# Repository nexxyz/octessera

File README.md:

# Octessera

Octessera turns cellular automata into music you can play.

It is a collection of small algorithmic musical world-bubbles. Set up a few
systems, combine them, nudge them, anchor them with a little sequencing, and
perform with the result in real time. The little rule-based worlds surprise
you, and you decide which surprises to keep.

## Start here

- [Try the simulator](userdocs/desktop-simulator.md): make a sound without
  building any hardware.
- [Build the instrument](userdocs/hardware/assembly-manual.md): assemble a
  standalone Octessera around a Raspberry Pi Zero 2 W or an Orange Pi Zero 2W.

The standalone instrument is built on exactly one of those two boards, with an
8x8 light-up grid, four keys, encoders, an OLED, and a DAC. The desktop
simulator mirrors the same instrument, so you can explore it on a computer
before you warm up the soldering iron.

## What you can make

- Grow generative synth patterns from Life, Brain, Ant, Bounce, Raindrops, and
  other cellular-automata behaviors.
- Make hands-on drum sequences, load samples, and send parts to external MIDI
  gear.
- Layer up to eight instruments and let grid motion reshape another layer's
  pitch, filter, velocity, or probability through modulation.
- Route instruments directly or through FX buses, then shape the shared mix with
  bus and global effects.
- Use **Keys** to play a line live, and use **Play** pages to mix, pan, change
  trigger probability, move XY controls, and punch in momentary effects.

A first session might be a drifting `life` pattern under a hand-built drum
sequence, with a sampler providing the hits, a bus effect making room for the
synth, and a live Keys layer nudging the whole thing somewhere new.

## Two reading guides

- [User guide](userdocs/README.md): the simulator, building and setting up the
  hardware, making music, controls, and reference pages. Start here if you want
  to play or build one.
- [Technical guide](docs/README.md): architecture, contracts, the two fixed
  board paths, build and deployment tools, and provenance. Start here if you
  want to change the code.

## Notes

[License](LICENSE) · [Sample pack](https://github.com/stargatedaw/stargate-sample-pack) ·
[Hardware attributions](hardware/ATTRIBUTIONS.md) ·
[Third-party notices](THIRD_PARTY_NOTICES.md)

This project was created with AI assistance. Octessera itself, however, does not contain any AI.

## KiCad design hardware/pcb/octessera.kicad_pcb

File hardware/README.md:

# Hardware

This is the home for Octessera's canonical hardware sources and committed
fabrication outputs. Building one? Start with the [assembly
manual](../userdocs/hardware/assembly-manual.md) instead; this tree is the
workshop behind it.

## What's in here

- [`hardware/pcb/`](pcb/) is the canonical KiCad source and library tree.
- [`hardware/enclosure/`](enclosure/) is the canonical CadQuery, generator, test, wrapper,
  and workflow source tree.
- [`hardware/docs/`](docs/) holds the technical references:
  - [Pinout and connections](docs/pinout-and-connections.md): PCB nets, buses,
    addresses and the `J1` cable.
  - [Manual hardware test suite](docs/manual-hardware-test-suite.md):
    Raspberry bench bring-up without the OLED.
  - [Orange Pi Armbian bring-up](docs/orange-pi-armbian-bringup.md), the
    [Orange production reference](docs/orange-pi-production-reference.md) and
    [Orange UART0 input routing](docs/orange-pi-input-routing.md).
  - [Branding assets](docs/branding-assets.md): logo sources and where they end
    up.

## PCB outputs

[`hardware/pcb/gerber/`](pcb/gerber/) contains the committed fabrication output: Gerbers,
drill files, the KiCad job file, and [`gerber.zip`](pcb/gerber/gerber.zip).

## Enclosure outputs

The enclosure source tree includes
[`CAD_WORKFLOW.md`](enclosure/CAD_WORKFLOW.md) and the CadQuery generators,
tests, and wrappers. It commits four generated output sets of 18 files each:

- [`hardware/enclosure/step/`](enclosure/step/): STEP files;
- [`hardware/enclosure/stl/`](enclosure/stl/): printable STL files;
- [`hardware/enclosure/3mf-single-material/`](enclosure/3mf-single-material/): single-material 3MF files;
- [`hardware/enclosure/3mf-multicolor/`](enclosure/3mf-multicolor/): multicolor 3MF files.

The multicolor set is a complete print set: 12 authored two-material designs
plus six one-material support pieces.

Protective-case filenames are canonical and statusless (`protective_case_*`).
The design remains an unqualified check-fit prototype, not a drop-rated,
waterproof, or transport-qualified product.

## Attribution and notices

See also:

- [`hardware/ATTRIBUTIONS.md`](ATTRIBUTIONS.md)
- [`NOTICE`](../NOTICE)
- [`THIRD_PARTY_NOTICES.md`](../THIRD_PARTY_NOTICES.md)
- [`samples/upstream/LICENSE`](../samples/upstream/LICENSE)

## Release assets

GitHub Desktop and Pi release assets are built by the release workflows and are
not stored here. This tree contains the canonical hardware sources and
committed fabrication outputs only.

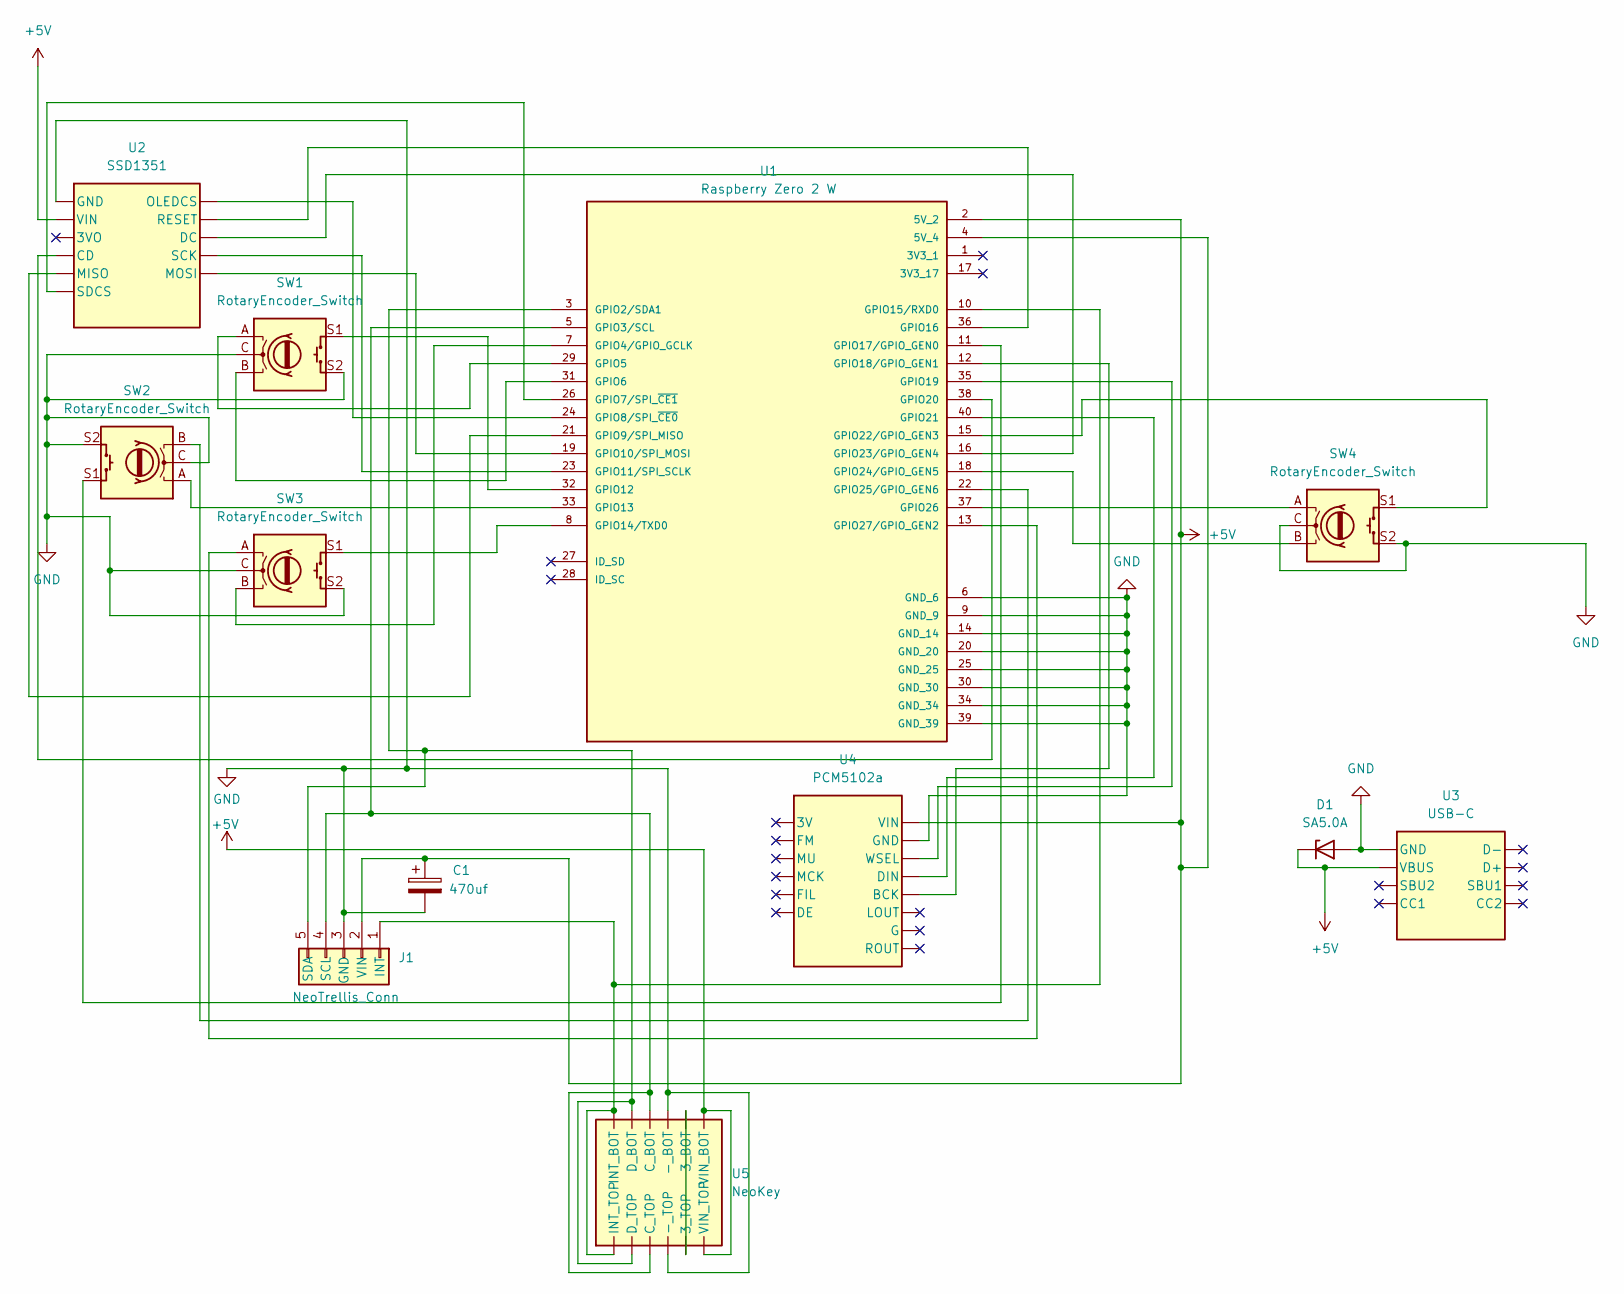
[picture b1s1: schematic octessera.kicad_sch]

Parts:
C1: 470uf; CP_Radial_D8.0mm_P3.50mm
D1: SA5.0A; D_DO-15_P10.16mm_Horizontal
J1: NeoTrellis_Conn; Adafruit_NeoTrellis_Connector_1x5
SW1, SW2, SW3, SW4: RotaryEncoder_Switch; RotaryEncoder_Alps_EC11E-Switch_Vertical_H20mm
U1: Raspberry Zero 2 W; MODULE_RASPBERRY_PI_ZERO_2_W; PARTREV April 2024
U2: SSD1351; Adafruit_SSD1351_OLED
U3: USB-C; Adafruit_USB_C_Breakout
U4: PCM5102a; Adafruit_PCM510x_I2S_DAC_6250
U5: NeoKey; Adafruit_NeoKey_1x4_QT

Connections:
+5V: C1.1, D1.1 (K), J1.2 (VIN), U1.2 (5V_2), U1.4 (5V_4), U2.+ (VIN), U3.VBUS, U4.VIN, U5.VIN (VIN_TOP)
GND: C1.2, D1.2 (A), J1.3 (GND), SW1.C, SW1.S2, SW2.C, SW2.S2, SW3.C, SW3.S2, SW4.C, SW4.S2, U1.6 (GND_6), U1.9 (GND_9), U1.14 (GND_14), U1.20 (GND_20), U1.25 (GND_25), U1.30 (GND_30), U1.34 (GND_34), U1.39 (GND_39), U2.G (GND), U3.GND, U4.GND, U5.- (-_TOP)
unnamed: J1.1 (INT), U1.10 (GPIO15/RXD0), U5.INT (INT_TOP)
unnamed: J1.4 (SCL), U1.5 (GPIO3/SCL), U5.C (C_TOP)
unnamed: J1.5 (SDA), U1.3 (GPIO2/SDA1), U5.D (D_TOP)
unnamed: SW3.B, U1.7 (GPIO4/GPIO_GCLK)
unnamed: SW1.A, U1.29 (GPIO5)
unnamed: SW1.B, U1.31 (GPIO6)
unnamed: U1.26 (GPIO7/SPI_~CE1), U2.SC (SDCS)
unnamed: U1.24 (GPIO8/SPI_~CE0), U2.OC (OLEDCS)
unnamed: U1.21 (GPIO9/SPI_MISO), U2.SO (MISO)
unnamed: U1.19 (GPIO10/SPI_MOSI), U2.SI (MOSI)
unnamed: U1.23 (GPIO11/SPI_SCLK), U2.CL (SCK)
unnamed: SW1.S1, U1.32 (GPIO12)
unnamed: SW2.A, U1.33 (GPIO13)
unnamed: SW3.S1, U1.8 (GPIO14/TXD0)
unnamed: U1.36 (GPIO16), U2.R (RESET)
unnamed: SW2.S1, U1.11 (GPIO17/GPIO_GEN0)
unnamed: U1.12 (GPIO18/GPIO_GEN1), U4.BCK
unnamed: U1.35 (GPIO19), U4.WSEL
unnamed: U1.38 (GPIO20), U2.CD
unnamed: U1.40 (GPIO21), U4.DIN
unnamed: SW4.S1, U1.15 (GPIO22/GPIO_GEN3)
unnamed: U1.16 (GPIO23/GPIO_GEN4), U2.DC
unnamed: SW4.B, U1.18 (GPIO24/GPIO_GEN5)
unnamed: SW2.B, U1.22 (GPIO25/GPIO_GEN6)
unnamed: SW4.A, U1.37 (GPIO26)
unnamed: SW3.A, U1.13 (GPIO27/GPIO_GEN2)

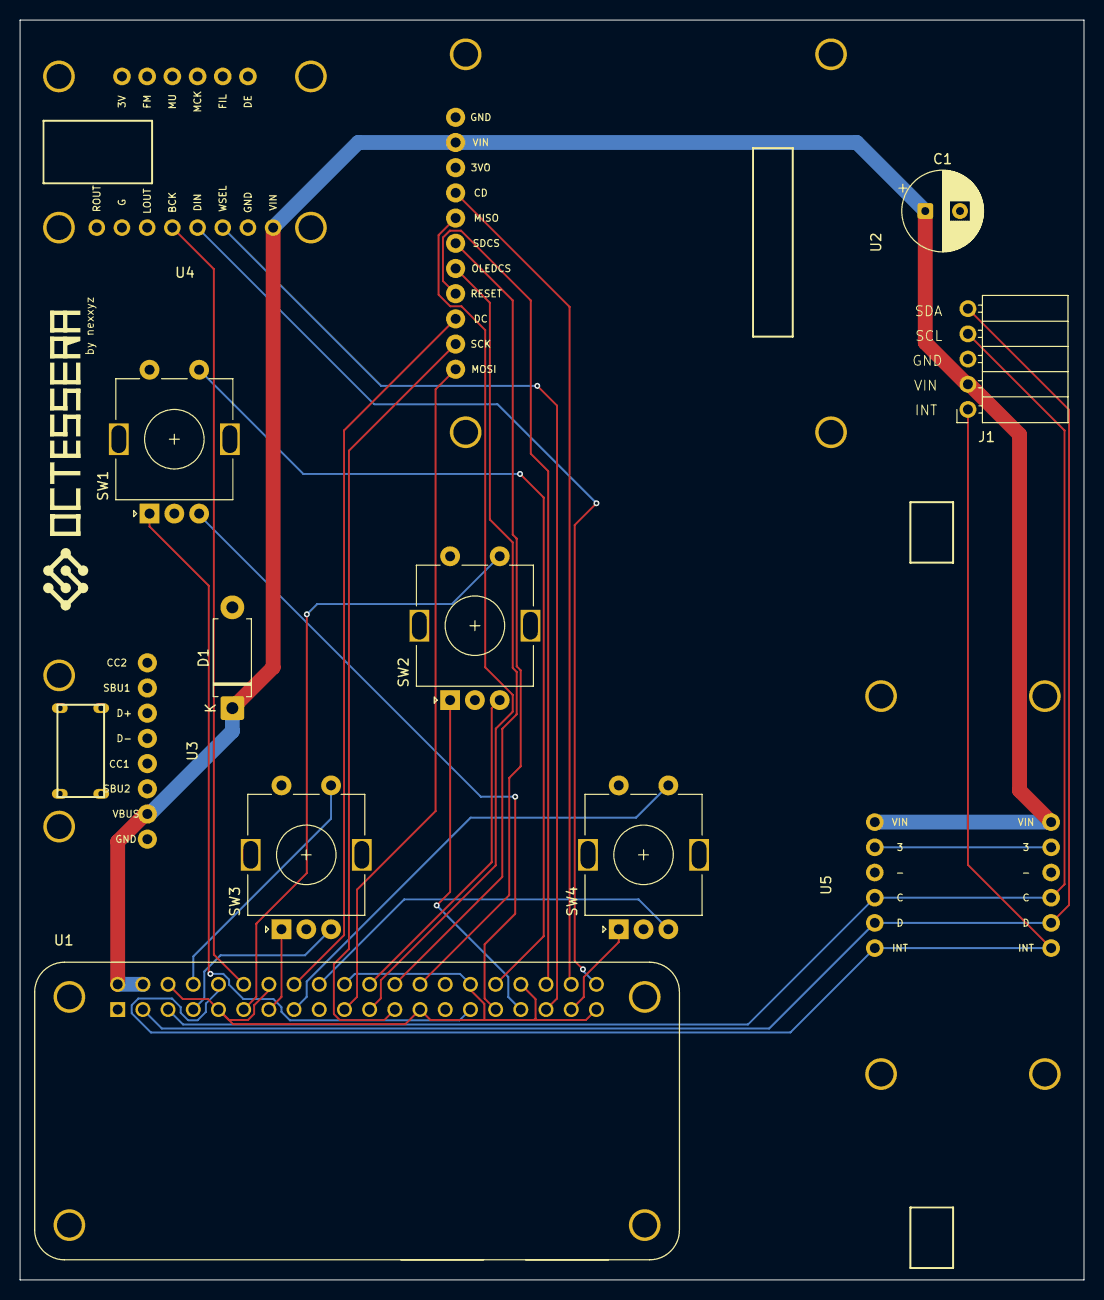
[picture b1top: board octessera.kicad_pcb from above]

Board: 2 copper layers, 107.2 x 127.0 mm, 12 parts (0 on the bottom side), 28 nets.
